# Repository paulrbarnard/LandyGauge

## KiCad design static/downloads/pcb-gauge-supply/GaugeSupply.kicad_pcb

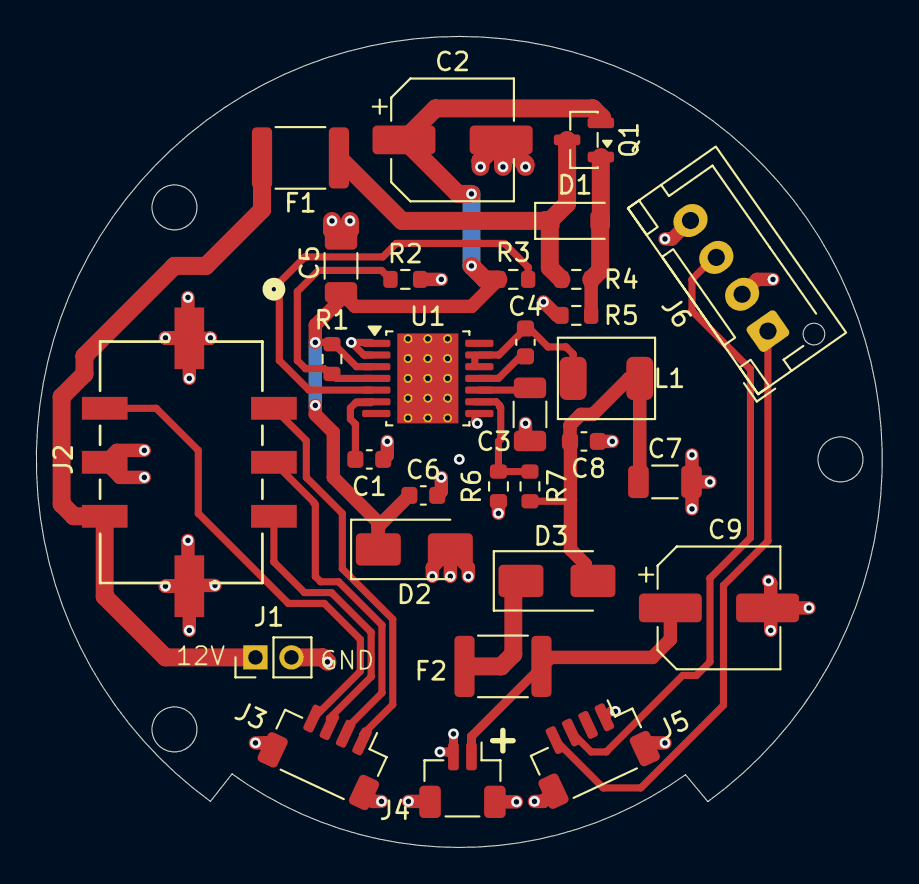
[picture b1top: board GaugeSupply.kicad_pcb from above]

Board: 2 copper layers, 47.0 x 45.1 mm, 30 parts (0 on the bottom side), 21 nets.

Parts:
C1, C4: 10n; C_0603_1608Metric
C2, C9: 47u; CP_Elec_6.3x4.5
C3, C5: 1u; C_1206_3216Metric
C6, C8: 0.1u; C_0603_1608Metric
C7: 22u X7R; C_1206_3216Metric
D1: BZT52B12; D_SOD-123F
D2: SMBJ58A; D_SMA
D3: SS34; D_SMA
F1, F2: MF-MSMF110-2; Fuse_1812_4532Metric
J1: 12V Supply; PinHeader_1x02_P2.00mm_Vertical
J2: Molex to expansion; CONN_SD-43045-007_06_MOL
J3: i2C; JST_SH_BM04B-SRSS-TB_1x04-1MP_P1.00mm_Vertical
J4: 5VSupply; JST_SH_BM02B-SRSS-TB_1x02-1MP_P1.00mm_Vertical
J5: IO; JST_SH_BM04B-SRSS-TB_1x04-1MP_P1.00mm_Vertical
J6: Buttons; JST_XH_B4B-XH-AM_1x04_P2.50mm_Vertical
L1: 10uH; L_Coilcraft_XAL4020-XXX
Q1: AO3401A; SOT-23
R1: 499k; R_0603_1608Metric
R2, R3, R4, R5: 100k; R_0603_1608Metric
R6: 22.1k; R_0603_1608Metric
R7: 33k; R_0603_1608Metric
U1: LM5161PWP; Texas_HTSSOP-14-1EP_4.4x5mm_P0.65mm_EP3.4x5mm_Mask3.155x3.2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

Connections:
5VSupply: C9.1, F2.1, J4.1
5V_OR: D3.1 (K), F2.2
+12V: F1.1, J1.1, J2.6
GND: C1.2, C2.2, C3.2, C5.2, C6.2, C7.2, C8.2, C9.2, D2.2 (A2), J1.2, J2.5, J2.7, J2.8, J3.MP, J4.2, J4.MP, J5.1, J5.MP, J6.2, J6.4, R2.2, R5.2, R6.2, U1.1 (AGND), U1.2 (PGND), U1.8 (FPWM), U1.15 (AGND)
unnamed: D1.2 (A), Q1.1 (G), R4.2, R5.1
unnamed: C7.1, C8.1, D3.2 (A), L1.2, R7.1
unnamed: J2.1, J3.1
unnamed: J2.2, J3.2
unnamed: J2.3, J3.3
unnamed: J2.4, J3.4
unnamed: C4.2, U1.11 (BST)
unnamed: R1.2, R2.1, U1.4 (EN/UVLO)
unnamed: R6.1, R7.2, U1.9 (FB)
unnamed: R3.2, U1.5 (RON)
unnamed: C1.1, U1.6 (SS)
unnamed: C3.1, U1.10 (VCC)
Next: J5.4, J6.1
Prev: J5.3, J6.3
SW_Node: C4.1, L1.1, U1.12 (SW), U1.13 (SW)
Vin_Fused: D1.1 (K), F1.2, Q1.3 (D), R4.1
Vin_Prot: C2.1, C5.1, C6.1, D2.1 (A1), Q1.2 (S), R1.1, R3.1, U1.3 (VIN)

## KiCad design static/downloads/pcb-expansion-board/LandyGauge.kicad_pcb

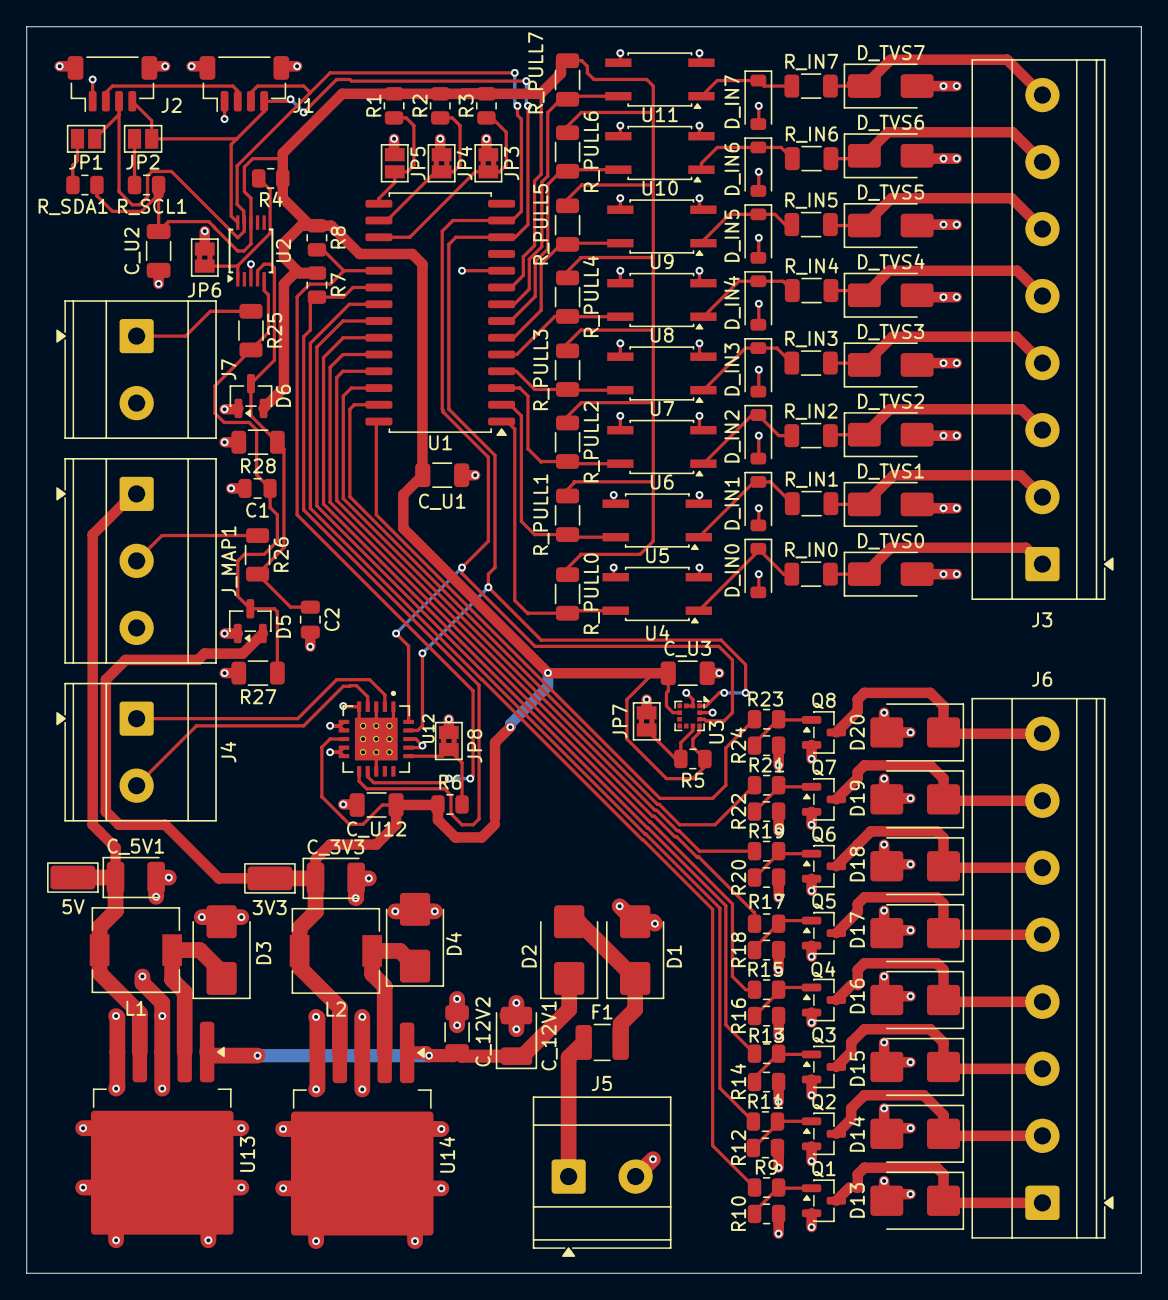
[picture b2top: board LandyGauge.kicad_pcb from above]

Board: 2 copper layers, 84.5 x 94.5 mm, 129 parts (0 on the bottom side), 75 nets.

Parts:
3V3, 5V: TestPoint_Keystone_5015_Micro_Mini
C1, C2: 100n; C_0805_2012Metric
C_3V3, C_5V1, C_12V1: 47u; CP_EIA-3528-21_Kemet-B
C_12V2: 100n; C_1206_3216Metric
C_U1, C_U2, C_U3, C_U12: 100n; C_1206_3216Metric
D1: SMBJ33A; D_SMB
D2, D3, D4: SS34; D_SMB
D5, D6: BAV99; SOT-23
D13, D14, D15, D16, D17, D18, D19, D20: SMBJ24CA; D_SMB
D_IN0, D_IN1, D_IN2, D_IN3, D_IN4, D_IN5, D_IN6, D_IN7: IN4148W; D_SOD-123
D_TVS0, D_TVS1, D_TVS2, D_TVS3, D_TVS4, D_TVS5, D_TVS6, D_TVS7: SMBJ16A; D_SMA
F1: MF-MSMF110; Fuse_1210_3225Metric
J1, J2: JST_SH_1x04_1.0; JST_SH_BM04B-SRSS-TB_1x04-1MP_P1.00mm_Vertical
J3, J6: 01x08 5.08 pitch horizontal screw terminal; TerminalBlock_Phoenix_MKDS-1,5-8-5.08_1x08_P5.08mm_Horizont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
J4, J5, J7: 01x02 5.08 pitch horizontal screw terminal; TerminalBlock_Phoenix_MKDS-3-2-5.08_1x02_P5.08mm_Horizontal
JP1: SDA PU; SolderJumper-2_P1.3mm_Open_Pad1.0x1.5mm
JP2: SCL PU; SolderJumper-2_P1.3mm_Open_Pad1.0x1.5mm
JP3: IO Add2; SolderJumper-2_P1.3mm_Bridged2Bar_Pad1.0x1.5mm
JP4: IO Add1; SolderJumper-2_P1.3mm_Bridged2Bar_Pad1.0x1.5mm
JP5: IO Add0; SolderJumper-2_P1.3mm_Open_Pad1.0x1.5mm
JP6: AD Add; SolderJumper-2_P1.3mm_Bridged2Bar_Pad1.0x1.5mm
JP7: MAG Add; SolderJumper-2_P1.3mm_Bridged2Bar_Pad1.0x1.5mm
JP8: THERM Add; SolderJumper-2_P1.3mm_Bridged2Bar_Pad1.0x1.5mm
J_MAP1: 01x03 5.08 pitch horizontal screw terminal; TerminalBlock_Phoenix_MKDS-3-3-5.08_1x03_P5.08mm_Horizontal
L1, L2: SRN6045-330M; L_6.3x6.3_H3
Q1, Q2, Q3, Q4, Q5, Q6, Q7, Q8: AOZ1304N; SOT-23
R1, R2, R3, R4, R5, R6, R7, R8: 10K; R_0805_2012Metric
R9, R11, R13, R15, R17, R19, R21, R23: 100R; R_0805_2012Metric
R10, R12, R14, R16, R18, R20, R22, R24: 100K; R_0805_2012Metric
R25: 1M; R_1206_3216Metric
R26: 47K; R_1206_3216Metric
R27: 330K; R_1206_3216Metric
R28: 33K; R_1206_3216Metric
R_IN0, R_IN1, R_IN2, R_IN3, R_IN4, R_IN5, R_IN6, R_IN7: 2K2; R_1206_3216Metric
R_PULL0, R_PULL1, R_PULL2, R_PULL3, R_PULL4, R_PULL5, R_PULL6, R_PULL7: 10K; R_1206_3216Metric
R_SCL1: 4K7; R_0805_2012Metric
R_SDA1: 4K7; R_0805_2012Metric
U1: MCP23017_SO; SOIC-28W_7.5x17.9mm_P1.27mm
U2: ADS1115IDGS; TSSOP-10_3x3mm_P0.5mm
U3: LIS3MDL; LGA-12_2x2mm_P0.5mm
U4, U5, U6, U7, U8, U9, U10, U11: EL817S1(C); SO-4_4.4x3.6mm_P2.54mm
U12: MCP9600-I_MX; QFN65P500X500X100-21N
U13: LM2596S-5; TO-263-5_TabPin3
U14: LM2596S-3.3; TO-263-5_TabPin3

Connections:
3V3_I2C: J1.2, J2.2
+3.3V: 3V3.1, C_3V3.1, C_U1.1, C_U2.1, C_U3.1, C_U12.1, D5.2 (A), D6.2 (A), L2.2, R1.1, R2.1, R3.1, R4.1, R5.1, R6.1, R7.1, R8.1, R_PULL0.1, R_PULL1.1, R_PULL2.1, R_PULL3.1, R_PULL4.1, R_PULL5.1, R_PULL6.1, R_PULL7.1, R_SCL1.1, R_SDA1.1, U1.9 (VDD), U1.18 (~RESET), U2.8 (VDD), U3.5 (Vdd), U3.10 (~CS), U12.8 (VDD), U14.4 (FB)
+12V: F1.1, J5.1
ADC_MAP: C2.1, D6.3 (K), R26.2, R28.1, U2.4 (AIN0)
GND: C1.2, C2.2, C_3V3.2, C_5V1.2, C_12V1.2, C_12V2.2, C_U1.2, C_U2.2, C_U3.2, C_U12.2, D1.2 (A), D3.2 (A), D4.2 (A), D5.1 (K), D6.1 (K), D13.2 (A2), D14.2 (A2), D15.2 (A2), D16.2 (A2), D17.2 (A2), D18.2 (A2), D19.2 (A2), D20.2 (A2), D_IN0.2 (A), D_IN1.2 (A), D_IN2.2 (A), D_IN3.2 (A), D_IN4.2 (A), D_IN5.2 (A), D_IN6.2 (A), D_IN7.2 (A), D_TVS0.2 (A2), D_TVS1.2 (A2), D_TVS2.2 (A2), D_TVS3.2 (A2), D_TVS4.2 (A2), D_TVS5.2 (A2), D_TVS6.2 (A2), D_TVS7.2 (A2), J1.1, J1.MP (MountPin), J2.1, J2.MP (MountPin), J5.2, J7.2, JP3.1 (A), JP4.1 (A), JP5.1 (A), JP6.2 (B), JP7.2 (B), JP8.2 (B), J_MAP1.3, Q1.2 (S), Q2.2 (S), Q3.2 (S), Q4.2 (S), Q5.2 (S), Q6.2 (S), Q7.2 (S), Q8.2 (S), R10.2, R12.2, R14.2, R16.2, R18.2, R20.2, R22.2, R24.2, R27.2, R28.2, U1.10 (VSS), U2.3 (GND), U3.2 (GND), U3.3 (GND), U3.12 (GND), U4.2, U4.3, U5.2, U5.3, U6.2, U6.3, U7.2, U7.3, U8.2, U8.3, U9.2, U9.3, U10.2, U10.3, U11.2, U11.3, U12.1 (GND), U12.3 (GND), U12.5 (GND), U12.6 (GND), U12.7 (GND), U12.9 (GND), U12.10 (GND), U12.13 (GND), U12.17 (GND), U12.18 (GND), U12.21 (EXP), U12.22 (EXP), U12.23 (EXP), U12.24 (EXP), U12.25 (EXP), U12.26 (EXP), U12.27 (EXP), U12.28 (EXP), U12.29 (EXP), U12.30 (EXP), U13.3 (GND), U13.5 (~ON/OFF), U14.3 (GND), U14.5 (~ON/OFF)
IN0: D_TVS0.1 (A1), J3.1, R_IN0.2
IN1: D_TVS1.1 (A1), J3.2, R_IN1.2
IN2: D_TVS2.1 (A1), J3.3, R_IN2.2
IN3: D_TVS3.1 (A1), J3.4, R_IN3.2
IN4: D_TVS4.1 (A1), J3.5, R_IN4.2
IN5: D_TVS5.1 (A1), J3.6, R_IN5.2
IN6: D_TVS6.1 (A1), J3.7, R_IN6.2
IN7: D_TVS7.1 (A1), J3.8, R_IN7.2
MAP_5V: 5V.1, C_5V1.1, J_MAP1.1, L1.2, U13.4 (FB)
MAP_SIG: J_MAP1.2, R26.1
unnamed: D1.1 (K), D2.2 (A), F1.2
unnamed: D3.1 (K), L1.1, U13.2 (OUT)
unnamed: D4.1 (K), L2.1, U14.2 (OUT)
unnamed: D_IN0.1 (K), R_IN0.1, U4.1
unnamed: D_IN1.1 (K), R_IN1.1, U5.1
unnamed: D_IN2.1 (K), R_IN2.1, U6.1
unnamed: D_IN3.1 (K), R_IN3.1, U7.1
unnamed: D_IN4.1 (K), R_IN4.1, U8.1
unnamed: D_IN5.1 (K), R_IN5.1, U9.1
unnamed: D_IN6.1 (K), R_IN6.1, U10.1
unnamed: D_IN7.1 (K), R_IN7.1, U11.1
unnamed: JP1.2 (B), R_SDA1.2
unnamed: JP2.2 (B), R_SCL1.2
unnamed: JP3.2 (B), R3.2, U1.17 (A2)
unnamed: JP4.2 (B), R2.2, U1.16 (A1)
unnamed: JP5.2 (B), R1.2, U1.15 (A0)
unnamed: JP6.1 (A), R4.2, U2.1 (ADDR)
unnamed: JP7.1 (A), R5.2, U3.9 (SDO/SA1)
unnamed: JP8.1 (A), R6.2, U12.16 (ADDR)
unnamed: Q1.1 (G), R9.2, R10.1
unnamed: Q2.1 (G), R11.2, R12.1
unnamed: Q3.1 (G), R13.2, R14.1
unnamed: Q4.1 (G), R15.2, R16.1
unnamed: Q5.1 (G), R17.2, R18.1
unnamed: Q6.1 (G), R19.2, R20.1
unnamed: Q7.1 (G), R21.2, R22.1
unnamed: Q8.1 (G), R23.2, R24.1
unnamed: R9.1, U1.21 (GPA0)
unnamed: R11.1, U1.22 (GPA1)
unnamed: R13.1, U1.23 (GPA2)
unnamed: R15.1, U1.24 (GPA3)
unnamed: R17.1, U1.25 (GPA4)
unnamed: R19.1, U1.26 (GPA5)
unnamed: R21.1, U1.27 (GPA6)
unnamed: R23.1, U1.28 (GPA7)
unnamed: R_PULL0.2, U1.1 (GPB0), U4.4
unnamed: R_PULL1.2, U1.2 (GPB1), U5.4
unnamed: R_PULL2.2, U1.3 (GPB2), U6.4
unnamed: R_PULL3.2, U1.4 (GPB3), U7.4
unnamed: R_PULL4.2, U1.5 (GPB4), U8.4
unnamed: R_PULL5.2, U1.6 (GPB5), U9.4
unnamed: R_PULL6.2, U1.7 (GPB6), U10.4
unnamed: R_PULL7.2, U1.8 (GPB7), U11.4
unnamed: R7.2, U1.20 (INTA), U12.11 (ALERT_1)
unnamed: R8.2, U1.19 (INTB), U12.12 (ALERT_2)
unnamed: C1.1, D5.3 (K), R25.2, R27.1, U2.5 (AIN1)
PROTO_12V: C_12V1.1, C_12V2.1, D2.1 (K), U13.1 (VIN), U14.1 (VIN)
RL0: D13.1 (A1), J6.1, Q1.3 (D)
RL1: D14.1 (A1), J6.2, Q2.3 (D)
RL2: D15.1 (A1), J6.3, Q3.3 (D)
RL3: D16.1 (A1), J6.4, Q4.3 (D)
RL4: D17.1 (A1), J6.5, Q5.3 (D)
RL5: D18.1 (A1), J6.6, Q6.3 (D)
RL6: D19.1 (A1), J6.7, Q7.3 (D)
RL7: D20.1 (A1), J6.8, Q8.3 (D)
SCL: J1.4, J2.4, JP2.1 (A), U1.12 (SCK), U2.10 (SCL), U3.1 (SCL/SPC), U12.19 (SCL)
SDA: J1.3, J2.3, JP1.1 (A), U1.13 (SDA), U2.9 (SDA), U3.11 (SDA/SDI/SDO), U12.20 (SDA)
TC+: J4.1, U12.2 (VIN+)
TC-: J4.2, U12.4 (VIN-)
TEMP_SIG: J7.1, R25.1

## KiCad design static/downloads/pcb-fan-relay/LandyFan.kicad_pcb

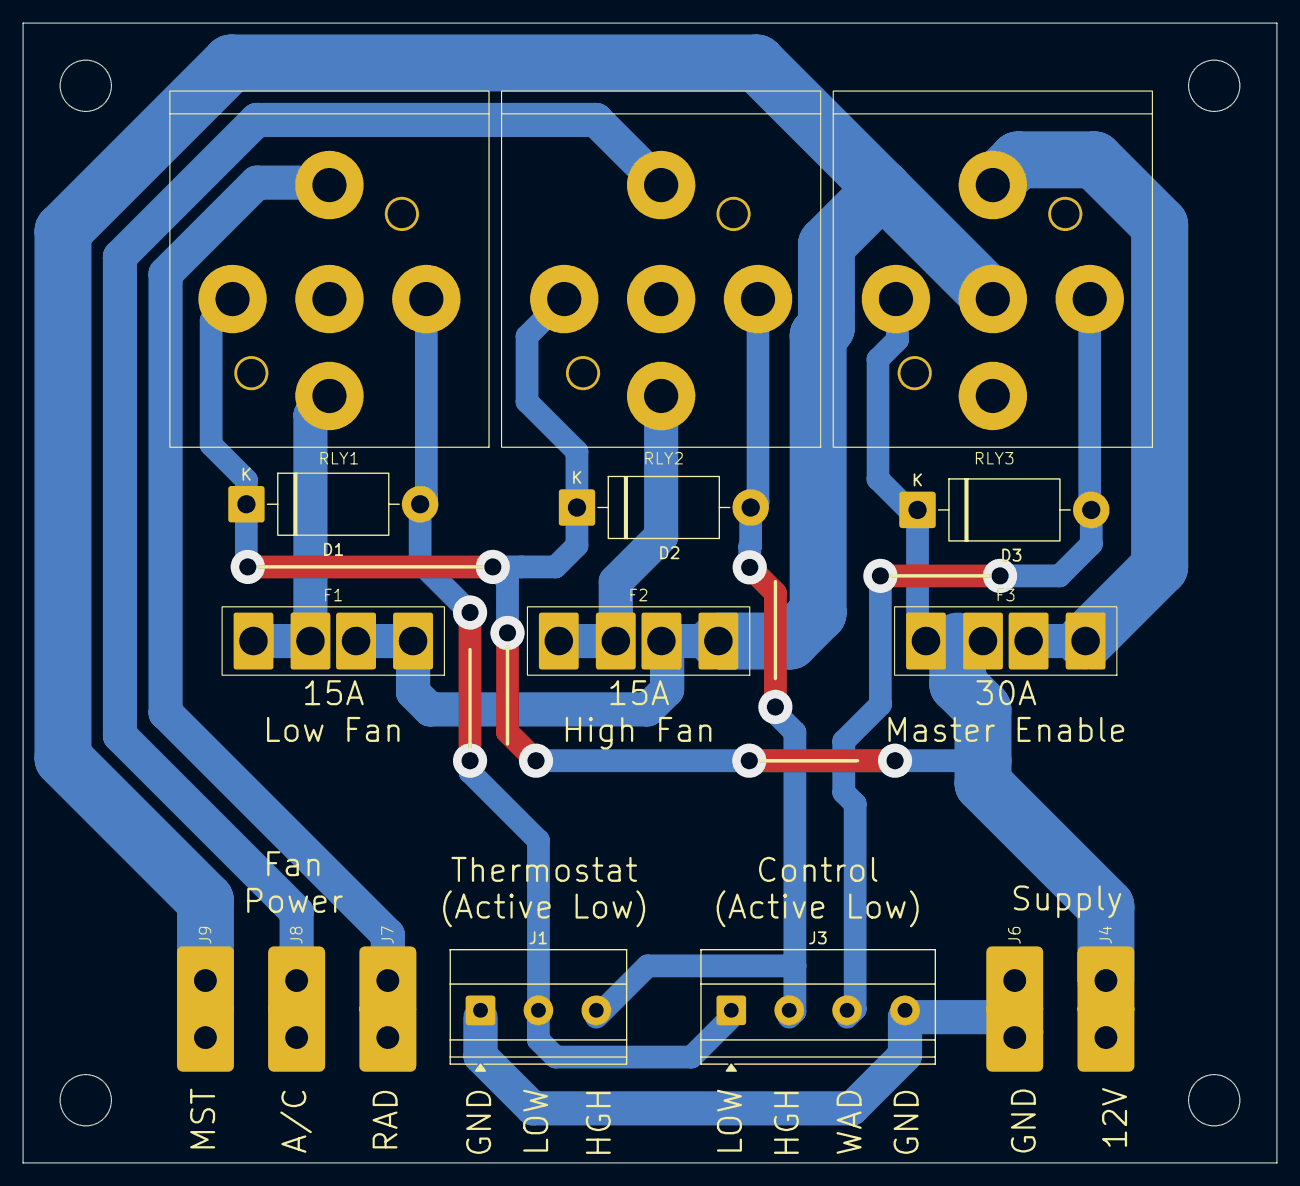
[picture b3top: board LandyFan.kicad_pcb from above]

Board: 2 copper layers, 110.0 x 100.0 mm, 16 parts (0 on the bottom side), 11 nets.

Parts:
D1, D2, D3: 1N5408; D_DO-201AD_P15.24mm_Horizontal
F1, F2: 15A; FuseHolder_Switch_Electronics
F3: 30A; FuseHolder_Switch_Electronics
J1: Thermal Switch; TerminalBlock_Phoenix_MKDS-1,5-3-5.08_1x03_P5.08mm_Horizont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
J3: Control; TerminalBlock_Phoenix_MKDS-1,5-4-5.08_1x04_P5.08mm_Horizont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
J4, J6, J7, J8, J9: Conn_01x01_Pin; FASTON .250 Spade
RLY1, RLY2, RLY3: Bosch Automotive Relay

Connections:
+12V: D1.1 (K), D2.1 (K), D3.1 (K), F3.2, J4.1, RLY1.85, RLY2.85, RLY3.85
GND: J1.1, J3.4, J6.1
HighFanEnable: D2.2 (A), J1.3, J3.2, RLY2.86
HighFanSupply: J8.1, RLY2.30
LowFanEnable: D1.2 (A), J1.2, J3.1, RLY1.86
LowFanSupply: J7.1, RLY1.30
MasterFanEnable: F1.1, F2.1, J9.1, RLY3.87a
unnamed: F1.2, RLY1.87
unnamed: F2.2, RLY2.87
unnamed: F3.1, RLY3.30
WaddingEnable: D3.2 (A), J3.3, RLY3.86

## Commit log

2026-04-20 Initial Hugo site scaffold with PaperMod theme
    - Site configuration for www.toxiccelery.co.uk
    - PaperMod theme (submodule)
    - Content: About, Hardware, Firmware, Build Guide pages
    - Blog section with launch post
    - GitHub Actions workflow for automatic Pages deployment
    - Navigation menu: About, Hardware, Firmware, Build Guide, Blog
2026-04-20 Add deployment and DNS setup guide
2026-04-20 Set GitHub username to paulrbarnard
2026-04-20 Switch domain to toxiccelery.com
2026-04-20 Add PCB schematics, 3D models, and wiring downloads
    - Gauge supply PCB (KiCad + gerbers + STEP)
    - Expansion board PCB (KiCad + gerbers + STEP + PDF)
    - Fan relay PCB (KiCad + gerbers + STEP)
    - Wiring schematic (KiCad + PDF)
    - 3D models: case, cover, bezels, nut, button plug (OBJ + Fusion 360)
    - Hardware page updated with download tables
2026-04-20 Update gauge supply gerbers (renamed to gerbers.zip)
2026-04-20 Add user manual page with nav menu link
2026-04-20 Add clock image to about page
2026-04-20 Update GitHub links to LandyGaugeFirmware repo
2026-04-20 Update about and hardware pages
2026-04-20 Replace expansion board gerbers with updated gerbers.zip
2026-04-21 Remove duplicate wiring schematic file
2026-04-21 Update site content and images
2026-04-22 Update homepage, hardware content, and 3D model downloads
2026-04-22 Update build guide, hardware docs, and connector images
2026-04-23 Update blog and build guide content
2026-04-23 Add Contact page with email address
2026-04-23 Update Actions workflow to use Node.js 24
